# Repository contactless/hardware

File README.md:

hardware
========

Contactless Devices hardware repo

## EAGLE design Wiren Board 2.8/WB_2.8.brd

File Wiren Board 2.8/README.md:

Wiren Board 2.8
===============

Eagle source files.

The description is available here: http://contactless.ru/wiki/index.php/Wiren_Board_2.8

(c) 2013-2014 Contactless Devices, LLC
http://contactless.ru

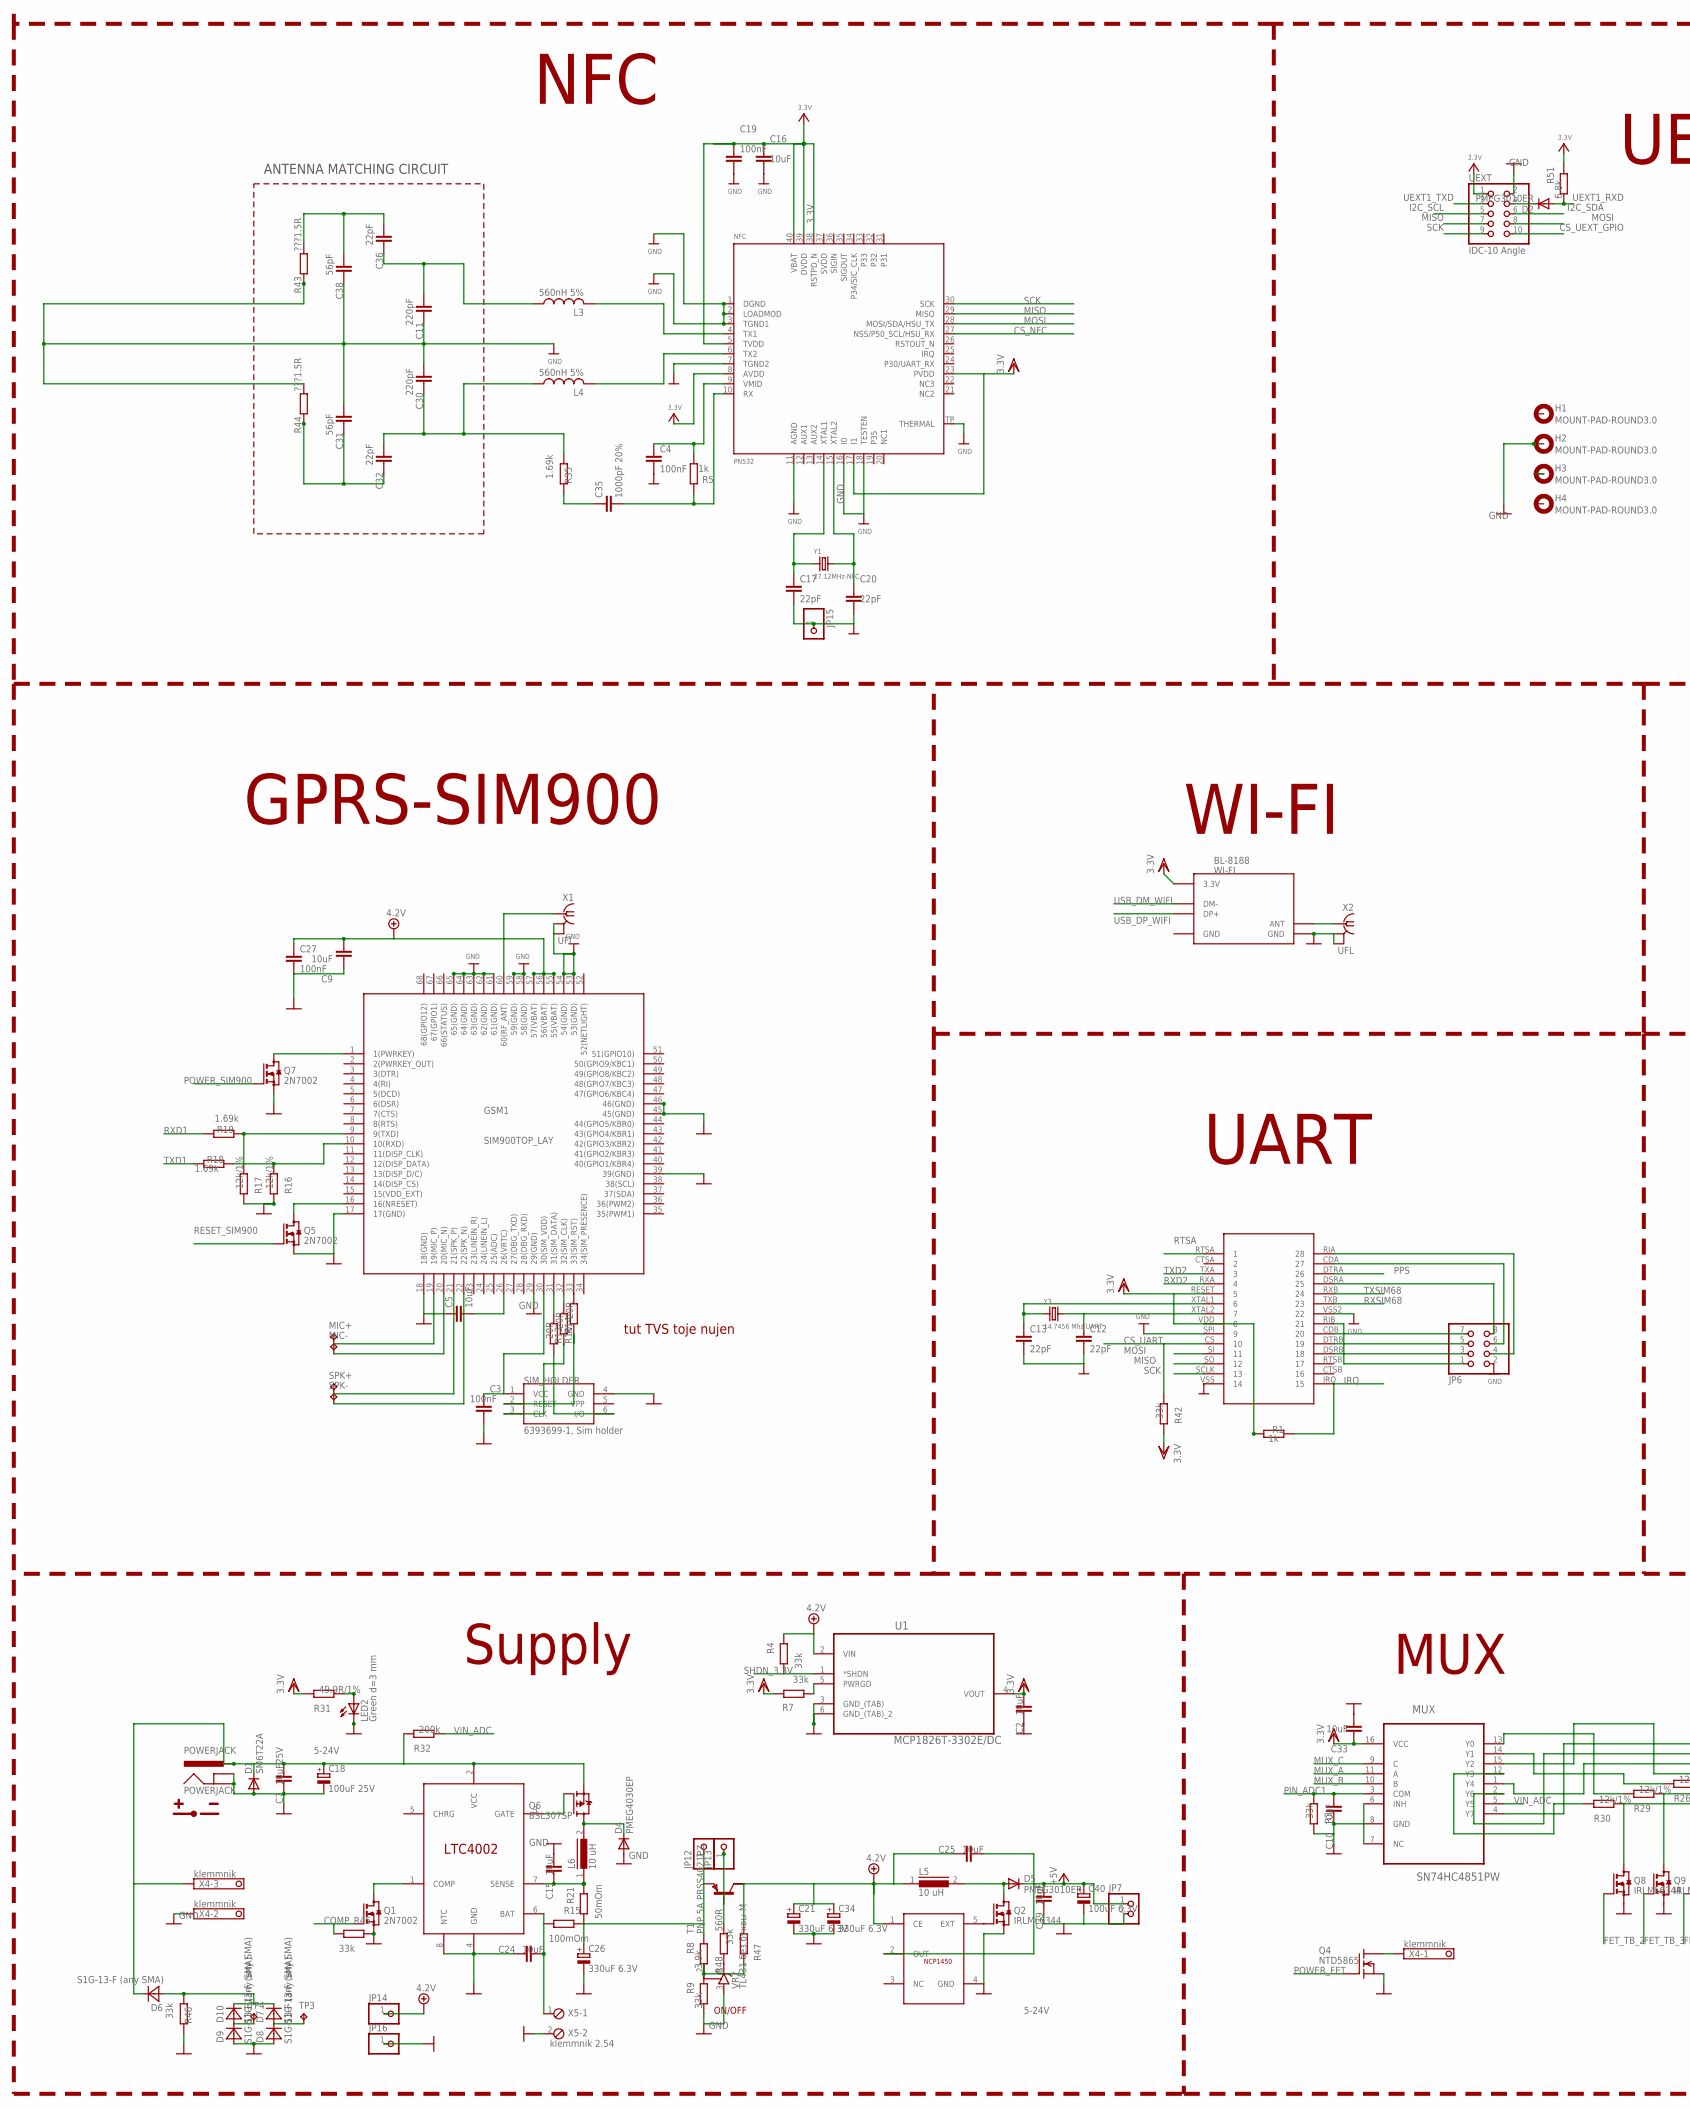
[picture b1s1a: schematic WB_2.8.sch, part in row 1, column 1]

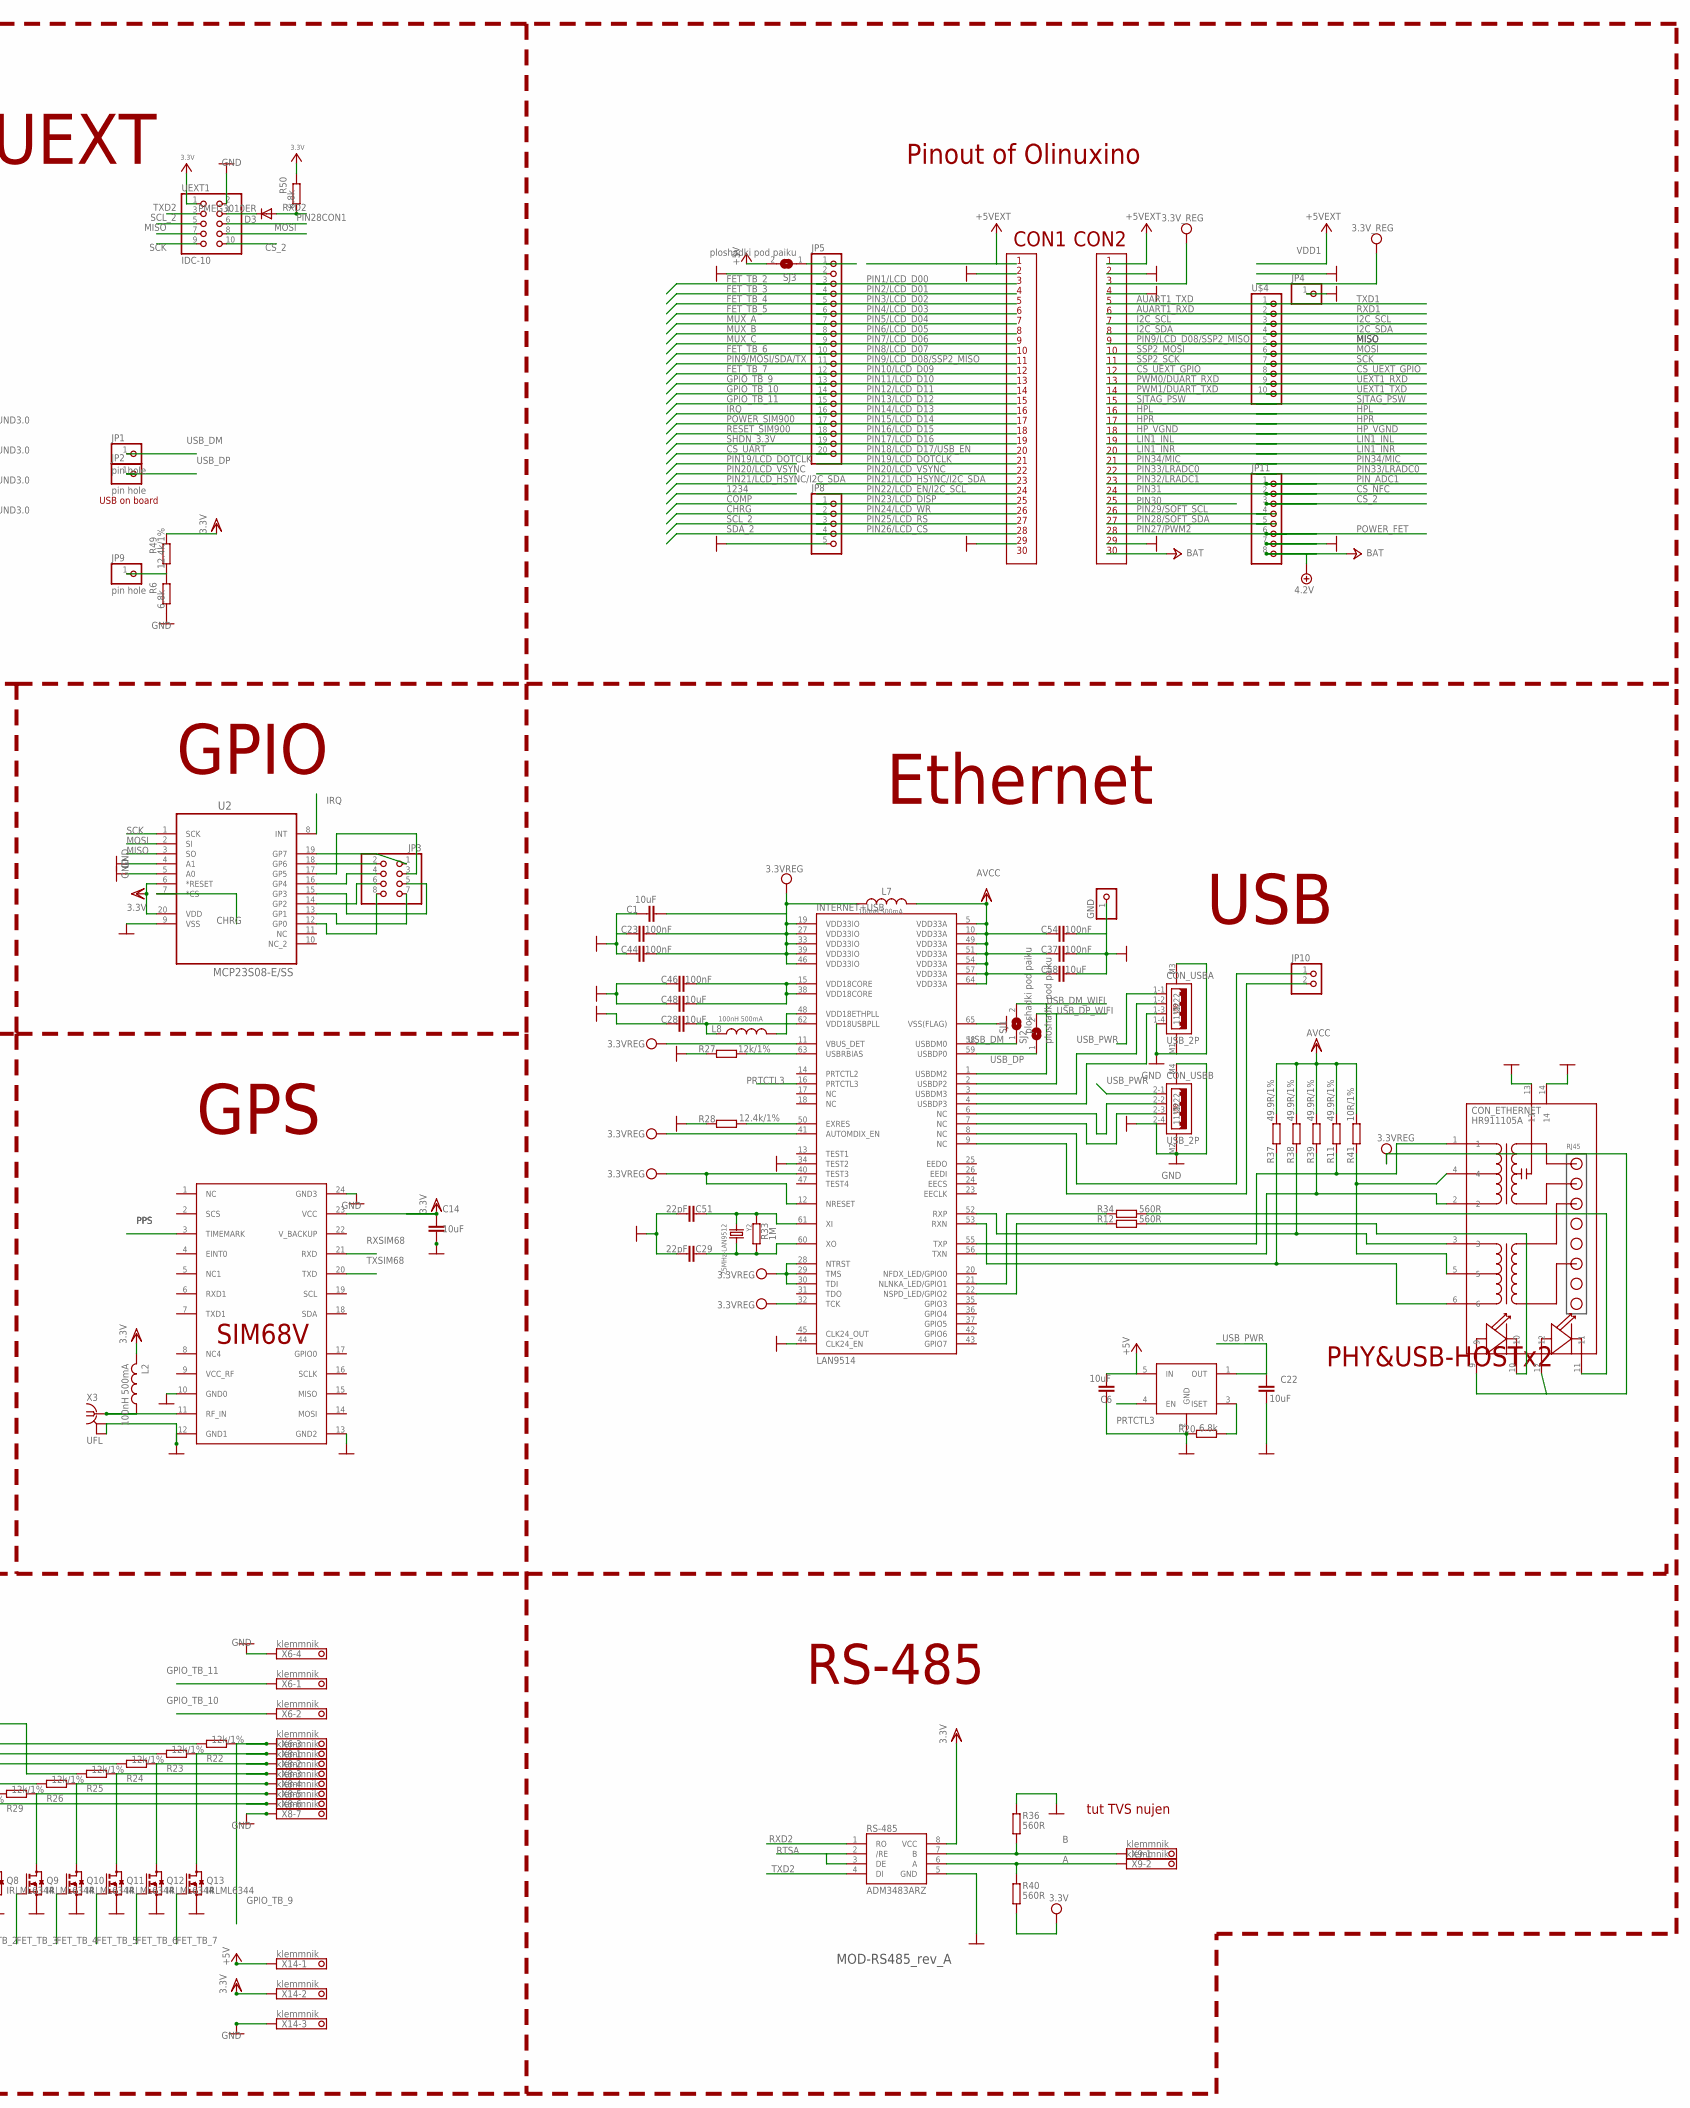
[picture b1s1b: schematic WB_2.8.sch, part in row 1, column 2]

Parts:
C1, C2, C5, C6, C9, C10, C14, C15, C16, C22, C24, C25, C28, C33, C39, C48, C58: 10uF; C0805_5MIL_D
C3, C4, C19, C23, C27, C37, C44, C46, C54: 100nF; C0805_5MIL_D
C7: 10uF25V; C0805_5MIL_D
C11, C30: 220pF; C0805_5MIL_D
C12, C13, C17, C20, C29, C32, C36, C51: 22pF; C0805_5MIL_D
C18: 100uF 25V; PANASONIC_D
C21, C26, C34: 330uF 6.3V; PANASONIC_D
C31, C38: 56pF; C0805_5MIL_D
C35: 1000pF 20%; C0805_5MIL_D
C40: 100uF 6.3V; PANASONIC_D
CON_ETHERNET: HR911105A
CON_USB: USB_2P; 2P
D1: SM6T22A; DO214AA
D2, D3, D5: PMEG3010ER; SOD123
D4: PMEG4030EP; DO214AC
D6, D7, D8, D9, D10: S1G-13-F (any SMA); SMA
GND: PINHD-1X1CB; 1X01-CLEANBIG
GSM1: SIM900TOP_LAY; SMT
H1, H2, H3, H4: MOUNT-PAD-ROUND3.0; 3,0-PAD
INTERNET+USB: LAN9514; QFN64
JP1, JP2: pin hole; 1X01@1
JP3, JP6: PINHD-2X4; 2X04
JP4, JP12, JP13: PINHD-1X1; 1X01
JP5: PINHD-1X20; 1X20
JP7, JP10: PINHD-1X2; 1X02
JP8: PINHD-1X5; 1X05
JP9: pin hole; 1X01
JP11: PINHD-1X8BIG; 1X08-BIG
JP14, JP16: PINHD-1X1; 1X01@1
JP15: PINHD-1X1CB; 1X01-CLEANBIG
L2, L7, L8: 100nH 500mA; L0805_5MIL_D
L3, L4: 560nH 5%; L0805_5MIL_D
L5, L6: 10 uH; DR74
LED2: Green d=3 mm; LED3MM
MIC+: PAD; TP20R
MIC-: PAD; TP20R
MUX: SN74HC4851PW; SOP65P640X120-16N
NFC: PN532; HVQFN40-6X6
POWERJACK: POWERJACK; 1
POWER_5V: NCP1450ASN50T1G; SO-6/4
Q1, Q5, Q7: 2N7002; SOT23
Q2, Q8, Q9, Q10, Q11, Q12, Q13: IRLML6344; SOT23
Q4: NTD5865; DPAK
Q6: BSL307SP; SC74_INFINEON
R1, R5: 1k; R0805_5MIL_D
R3, R4, R7, R9, R42, R45, R46, R47: 33k; R0805_5MIL_D
R6, R20, R50, R51: 6.8k; R0805_5MIL_D
R8: 3.9k; R0805_5MIL_D
R10, R13, R14: 20R; R0805_5MIL_D
R11, R31, R37, R38, R39: 49.9R/1%; R0805_5MIL_D
R12, R34, R36, R40, R48: 560R; R0805_5MIL_D
R15: 100mOm; R1206
R16, R17, R22, R23, R24, R25, R26, R27, R29, R30: 12k/1%; R0805_5MIL_D
R18, R19, R35: 1.69k; R0805_5MIL_D
R21: 50mOm; R1206
R28, R49: 12.4k/1%; R0805_5MIL_D
R32: 200k; R0805_5MIL_D
R33: 1M; R0805_5MIL_D
R41: 10R/1%; R0805_5MIL_D
R43, R44: ???1.5R; R0805_5MIL_D
RS-485: ADM3483ARZ; SOIC8
SIM68: SIM68; SIM68V
SIM_HOLDER: 6393699-1, Sim holder; BIGSIM
SJ1, SJ2, SJ3: ploshadki pod paiku; SJ
SPK+: PAD; TP20R
SPK-: PAD; TP20R
T1: PNP 5A PBSS4021PZ; SOT223
TP3, TP4: contact for POE; B1,27
U1: MCP1826T-3302E/DC; SOT230P700X180-6N
U2: MCP23S08-E/SS; SOP65P780X200-20N
U$3: LTC4002ES8-4.2; SOIC-8
U$4: PINHD-1X10; 1X10-BIG
U$15: SY6280; SOT23-5L
UART: !SC16IS752; TSSOP28
UEXT: IDC-10 Angle; 2X05/90
UEXT1: IDC-10; 2X05
VR2: TL431 без буквы M; SOT23
WI-FI: BL-8188; BL-8188-PACK
X1, X2, X3: UFL; MC-921
X4, X14: klemmnik; 1751251
X5: klemmnik 2.54; 2POL254
X6: klemmnik; 1751264
X8: klemmnik; 1751293
X9: klemmnik; 1751248
Y1: 27.12MHz-NFC; CRYSTAL_3.2X2.5
Y2: 25MHz-LAN9512; CRYSTAL_3.2X2.5
Y3: 14.7456 Mhz UART; CRYSTAL_3.2X2.5

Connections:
3.3V: C1.2, C2.2, C14.1, C16.1, C19.1, C23.2, C33.1, C44.2, CON_ETHERNET.9, CON_ETHERNET.12, INTERNET+USB.11 (VBUS_DET), INTERNET+USB.12 (NRESET), INTERNET+USB.19 (VDD33IO), INTERNET+USB.27 (VDD33IO), INTERNET+USB.28 (NTRST), INTERNET+USB.29 (TMS), INTERNET+USB.30 (TDI), INTERNET+USB.32 (TCK), INTERNET+USB.33 (VDD33IO), INTERNET+USB.39 (VDD33IO), INTERNET+USB.40 (TEST3), INTERNET+USB.41 (AUTOMDIX_EN), INTERNET+USB.46 (VDD33IO), L2.2, L7.1, MUX.16 (VCC), NFC.5 (TVDD), NFC.8 (AVDD), NFC.17 (I1), NFC.23 (PVDD), NFC.38 (RSTPD_N), NFC.39 (DVDD), NFC.40 (VBAT), R1.2, R7.2, R31.1, R40.1, R42.1, R49.2, R50.2, R51.2, RS-485.8 (VCC), SIM68.23 (VCC), U1.4 (VOUT), U2.6 (*RESET), U2.20 (VDD), UART.RESET (5), UART.VDD (8), UEXT.1, UEXT1.1, WI-FI.3.3V, X14.2
5-24V: C7.2, C18.+, D1.C, D6.C, POWERJACK.1 (PWR), Q6.4 (S), R32.1, U$3.2 (VCC), X4.3
15(VDD_EXT): GSM1.15 (15(VDD_EXT))
+4.1V: C9.2, C21.+, C25.1, C27.1, C34.+, GSM1.55 (55(VBAT)), GSM1.56 (56(VBAT)), GSM1.57 (57(VBAT)), JP11.8, JP14.1, L5.1, POWER_5V.1 (CE), R4.2, R47.1, T1.4 (C1), U1.2 (VIN)
+5V: C6.1, C25.2, C39.2, C40.+, D5.C, JP7.1, POWER_5V.2 (OUT), SJ3.2, U$15.5 (IN), X14.1
A: R40.2, RS-485.6 (A), X9.2
B: R36.1, RS-485.7 (B), X9.1
CHRG: JP8.2, U2.7 (*CS)
COMP: JP8.1, Q1.1 (G), R45.1
CS_2: JP11.3, UEXT1.10
CS_NFC: JP11.2, NFC.27 (NSS/P50_SCL/HSU_RX)
CS_UART: JP5.20, R42.2, UART.CS (10)
CS_UEXT_GPIO: U$4.8, UEXT.10
DFGSDFG: Q13.3 (D), R23.2, X8.1
DFTGSDFG: MUX.15 (Y2), R25.1
ERTERVT: MUX.12 (Y3), R30.1
FDSGSDFGSDF: JP11.5
FET_TB_2: JP5.3, Q8.1 (G)
FET_TB_3: JP5.4, Q9.1 (G)
FET_TB_4: JP5.5, Q10.1 (G)
FET_TB_5: JP5.6, Q11.1 (G)
FET_TB_6: JP5.10, Q12.1 (G)
FET_TB_7: JP5.12, Q13.1 (G)
GND: C1.1, C2.1, C3.2, C4.2, C5.1, C6.2, C7.1, C9.1, C10.1, C11.1, C12.2, C13.2, C14.2, C15.2, C16.2, C17.2, C18.-, C19.2, C20.2, C21.-, C22.2, C23.1, C24.1, C26.-, C27.2, C28.1, C29.2, C30.2, C31.2, C33.2, C34.-, C37.2, C38.1, C39.1, C40.-, C44.1, C46.1, C48.1, C51.2, C54.2, C58.2, CON_ETHERNET.13, CON_ETHERNET.14, CON_USB.1-4 (4), CON_USB.2-4 (4), CON_USB.M1 (1111), CON_USB.M2 (1111), CON_USB.M3 (2222), CON_USB.M4 (2222), D1.A, D4.A, D8.A, D9.A, GND.1, GSM1.17 (17(GND)), GSM1.18 (18(GND)), GSM1.29 (29(GND)), GSM1.39 (39(GND)), GSM1.45 (45(GND)), GSM1.46 (46(GND)), GSM1.53 (53(GND)), GSM1.54 (54(GND)), GSM1.58 (58(GND)), GSM1.59 (59(GND)), GSM1.61 (61(GND)), GSM1.62 (62(GND)), GSM1.63 (63(GND)), GSM1.64 (64(GND)), GSM1.65 (65(GND)), H2.B3,0, INTERNET+USB.34 (TEST2), INTERNET+USB.44 (CLK24_EN), INTERNET+USB.65 (VSS(FLAG)), JP4.1, JP5.2, JP6.2, JP7.2, JP8.5, JP11.7, JP15.1, JP16.1, LED2.K (C), MUX.6 (INH), MUX.7 (NC), MUX.8 (GND), NFC.1 (DGND), NFC.2 (LOADMOD), NFC.3 (TGND1), NFC.7 (TGND2), NFC.11 (AGND), NFC.16 (I0), NFC.18 (TESTEN), NFC.TP (THERMAL), POWERJACK.P$1 (GNDBREAK), POWERJACK.P$5 (GND), POWER_5V.4 (GND), Q1.2 (S), Q2.2 (S), Q4.3 (S), Q5.2 (S), Q7.2 (S), Q8.2 (S), Q9.2 (S), Q10.2 (S), Q11.2 (S), Q12.2 (S), Q13.2 (S), R3.1, R6.1, R9.1, R16.1, R17.1, R20.1, R27.1, R28.1, R36.2, R43.1, R44.2, R45.2, R46.1, RS-485.5 (GND), SIM68.10 (GND0), SIM68.12 (GND1), SIM68.13 (GND2), SIM68.24 (GND3), SIM_HOLDER.4 (GND), U1.3 (GND_(TAB)), U1.6 (GND_(TAB)_2), U2.4 (A1), U2.5 (A0), U2.9 (VSS), U$3.4 (GND), U$3.8 (NTC), U$15.2 (GND), UART.SPI (9), UART.VSS (14), UART.VSS2 (22), UEXT.2, UEXT1.2, VR2.3 (A), WI-FI.GND1 (GND), WI-FI.GND2 (GND), X1.2@1 (GND), X1.2@2 (GND), X2.2@1 (GND), X2.2@2 (GND), X3.2@1 (GND), X3.2@2 (GND), X4.2, X5.2, X6.4, X8.7, X14.3
GPIO_TB_9: JP5.13, R22.2, X6.3
GPIO_TB_10: JP5.14, X6.2
GPIO_TB_11: JP5.15, X6.1
I2C_SCL: U$4.3, UEXT.5
I2C_SDA: U$4.4, UEXT.6
IRQ: JP5.16, R1.1, U2.8 (INT), UART.IRQ (15)
MISO: NFC.29 (MISO), U2.3 (SO), U$4.5, UART.SO (12), UEXT.7, UEXT1.7
MOSI: NFC.28 (MOSI/SDA/HSU_TX), U2.2 (SI), U$4.6, UART.SI (11), UEXT.8, UEXT1.8
MUX_A: JP5.7, MUX.11 (A)
MUX_B: JP5.8, MUX.10 (B)
MUX_C: JP5.9, MUX.9 (C)
unnamed: L3.2, NFC.4 (TX1)
unnamed: L4.2, NFC.6 (TX2)
unnamed: C11.2, C36.1, L3.1
unnamed: GSM1.16 (16(NRESET)), Q5.3 (D)
unnamed: JP13.1, R48.2, T1.1 (B)
unnamed: GSM1.9 (9(TXD)), R17.2, R19.1
unnamed: C17.1, NFC.14 (XTAL1), Y1.1
unnamed: C20.1, NFC.15 (XTAL2), Y1.2
unnamed: C35.1, R35.1
unnamed: C4.1, NFC.9 (VMID), R5.2
unnamed: C35.2, NFC.10 (RX), R5.1
unnamed: C30.1, C32.2, L4.1, R35.2
unnamed: R10.1, SIM_HOLDER.6 (I/O)
unnamed: GSM1.33 (33(SIM_RST)), R14.2
unnamed: R13.1, SIM_HOLDER.3 (CLK)
unnamed: WI-FI.ANT, X2.1
unnamed: R14.1, SIM_HOLDER.2 (RESET)
unnamed: C26.+, JP12.1, R8.2, R15.2, R21.1, T1.3 (E)
unnamed: GSM1.31 (31(SIM_DATA)), R10.2
unnamed: GSM1.1 (1(PWRKEY)), Q7.3 (D)
unnamed: C5.2, GSM1.26 (26(VRTC))
unnamed: GSM1.60 (60(RF_ANT)), X1.1
unnamed: Q6.3 (G), U$3.3 (GATE)
unnamed: C46.2, C48.2, INTERNET+USB.15 (VDD18CORE), INTERNET+USB.38 (VDD18CORE)
unnamed: JP6.3, UART.DSRB (18)
unnamed: GSM1.32 (32(SIM_CLK)), R13.2
unnamed: L2.1, SIM68.11 (RF_IN), X3.1
unnamed: C13.1, UART.XTAL1 (6), Y3.1
unnamed: C12.1, UART.XTAL2 (7), Y3.2
unnamed: C3.1, GSM1.30 (30(SIM_VDD)), SIM_HOLDER.1 (VCC)
unnamed: Q4.4 (D), X4.1
unnamed: GSM1.10 (10(RXD)), R16.2, R18.1
unnamed: JP3.1, U2.19 (GP7)
unnamed: INTERNET+USB.48 (VDD18ETHPLL), L8.2
unnamed: C28.2, INTERNET+USB.62 (VDD18USBPLL), L8.1
unnamed: INTERNET+USB.63 (USBRBIAS), R27.2
unnamed: INTERNET+USB.50 (EXRES), R28.2
unnamed: R48.1, VR2.1 (C)
unnamed: MUX.1 (Y4), R24.1
unnamed: R20.2, U$15.3 (ISET)
unnamed: Q12.3 (D), R24.2, X8.2
unnamed: Q11.3 (D), R25.2, X8.3
unnamed: Q10.3 (D), R26.2, X8.4
unnamed: Q9.3 (D), R29.2, X8.5
unnamed: Q8.3 (D), R30.2, X8.6
unnamed: C15.1, L6.1, R21.2, U$3.7 (SENSE)
unnamed: MUX.4 (Y7), R22.1
unnamed: MUX.2 (Y6), R23.1
unnamed: D7.A, D8.C, TP3.TP
unnamed: LED2.A, R31.2
unnamed: MUX.14 (Y1), R26.1
unnamed: D4.C, L6.2, Q6.1 (D), Q6.2 (D), Q6.5 (D), Q6.6 (D)
unnamed: C51.1, INTERNET+USB.61 (XI), R33.2, Y2.1
unnamed: C29.1, INTERNET+USB.60 (XO), R33.1, Y2.2
unnamed: INTERNET+USB.21 (NLNKA_LED/GPIO1), R34.1
unnamed: INTERNET+USB.22 (NSPD_LED/GPIO2), R12.1
unnamed: CON_ETHERNET.11, R34.2
unnamed: POWER_5V.5 (EXT), Q2.1 (G)
unnamed: CON_ETHERNET.6, INTERNET+USB.53 (RXN), R37.1
unnamed: CON_ETHERNET.3, INTERNET+USB.52 (RXP), R38.1
unnamed: CON_ETHERNET.2, INTERNET+USB.56 (TXN), R39.1
unnamed: CON_ETHERNET.1, INTERNET+USB.55 (TXP), R11.1
unnamed: CON_ETHERNET.4, CON_ETHERNET.5, R41.1
unnamed: CON_USB.1-2 (2), INTERNET+USB.3 (USBDM3)
unnamed: CON_USB.1-3 (3), INTERNET+USB.4 (USBDP3)
unnamed: CON_USB.2-2 (2), INTERNET+USB.6 (NC)
unnamed: CON_USB.2-3 (3), INTERNET+USB.7 (NC)
unnamed: D9.C, D10.A, TP4.TP
unnamed: GSM1.19 (19(MIC_P)), MIC+.TP
unnamed: GSM1.20 (20(MIC_N)), MIC-.TP
unnamed: D5.A, L5.2, Q2.3 (D)
unnamed: D6.A, D7.C, D10.C, R46.2
unnamed: CON_ETHERNET.10, R12.2
unnamed: GSM1.21 (21(SPK_P)), SPK+.TP
unnamed: GSM1.22 (22(SPK_N)), SPK-.TP
unnamed: Q1.3 (D), U$3.1 (COMP)
unnamed: R8.1, R9.2, R47.2, VR2.2 (R)
unnamed: JP9.1, R6.2, R49.1
unnamed: INTERNET+USB.8 (NC), JP10.1
unnamed: INTERNET+USB.9 (NC), JP10.2
unnamed: JP6.1, UART.RIB (21)
unnamed: JP6.5, UART.DTRB (19)
unnamed: JP6.7, UART.CDB (20)
unnamed: MUX.13 (Y0), R29.1
unnamed: C24.2, R15.1, U$3.6 (BAT), X5.1
unnamed: R7.1, U1.5 (PWRGD)
unnamed: JP3.2, U2.18 (GP6)
unnamed: JP3.3, U2.17 (GP5)
unnamed: JP6.8, UART.DSRA (25)
unnamed: JP6.6, UART.CDA (27)
unnamed: JP6.4, UART.RIA (28)
unnamed: JP3.4, U2.16 (GP4)
unnamed: JP3.5, U2.15 (GP3)
unnamed: JP3.6, U2.14 (GP2)
unnamed: JP3.7, U2.13 (GP1)
unnamed: JP3.8, U2.12 (GP0)
unnamed: JP5.1, SJ3.1
unnamed: D2.C, UEXT.4
unnamed: D3.C, UEXT1.4
PIN9/MOSI/SDA/TX: JP5.11
PIN28CON1: UEXT1.6
PIN29/SOFT_SCL: JP11.4
PIN_ADC1: C10.2, JP11.1, MUX.3 (COM), R3.2
POWER_FET: JP11.6, Q4.1 (G)
POWER_SIM900: JP5.17, Q7.1 (G)
PPS: SIM68.3 (TIMEMARK), UART.DTRA (26)
PRTCTL3: INTERNET+USB.16 (PRTCTL3), U$15.4 (EN)
RESET_SIM900: JP5.18, Q5.1 (G)
RTSA: RS-485.2 (/RE), RS-485.3 (DE), UART.RTSA (1)
RXD1: R19.2, U$4.2
RXD2: D3.A, R50.1, RS-485.1 (RO), UART.RXA (4)
RXSIM68: SIM68.21 (RXD), UART.TXB (23)
SCK: NFC.30 (SCK), U2.1 (SCK), U$4.7, UART.SCLK (13), UEXT.9, UEXT1.9
SCL_2: JP8.3, UEXT1.5
SDA_2: JP8.4
SHDN_3.3V: JP5.19, R4.1, U1.1 (*SHDN)
TX1_ANTENNA: C36.2, C38.2, R43.2
TX2_ANTENNA: C31.1, C32.1, R44.1
TXD1: R18.2, U$4.1
TXD2: RS-485.4 (DI), UART.TXA (3), UEXT1.3
TXSIM68: SIM68.20 (TXD), UART.RXB (24)
UEXT1_RXD: D2.A, R51.1, U$4.9
UEXT1_TXD: U$4.10, UEXT.3
USB_DM: INTERNET+USB.58 (USBDM0), JP1.1, SJ1.1
USB_DM_WIFI: INTERNET+USB.1 (USBDM2), SJ1.2, WI-FI.DM-
USB_DP: INTERNET+USB.59 (USBDP0), JP2.1, SJ2.1
USB_DP_WIFI: INTERNET+USB.2 (USBDP2), SJ2.2, WI-FI.DP+
USB_PWR: C22.1, CON_USB.1-1 (1), CON_USB.2-1 (1), U$15.1 (OUT)
VCC_RF: SIM68.9 (VCC_RF)
VDD: C37.1, C54.1, C58.1, INTERNET+USB.5 (VDD33A), INTERNET+USB.10 (VDD33A), INTERNET+USB.49 (VDD33A), INTERNET+USB.51 (VDD33A), INTERNET+USB.54 (VDD33A), INTERNET+USB.57 (VDD33A), INTERNET+USB.64 (VDD33A), L7.2, R11.2, R37.2, R38.2, R39.2, R41.2
VIN_ADC: MUX.5 (Y5), R32.2

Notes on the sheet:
ANTENNA MATCHING CIRCUIT
NFC
UEXT
GPRS-SIM900
WI-FI
UART
GPS
Ethernet
USB
PHY&USB-HOSTx2
Supply
MUX
MOD-RS485_rev_A
RS-485
USB on board
ON/OFF
Pinout of Olinuxino
CON1
CON2
GPIO
tut TVS nujen
tut TVS toje nujen

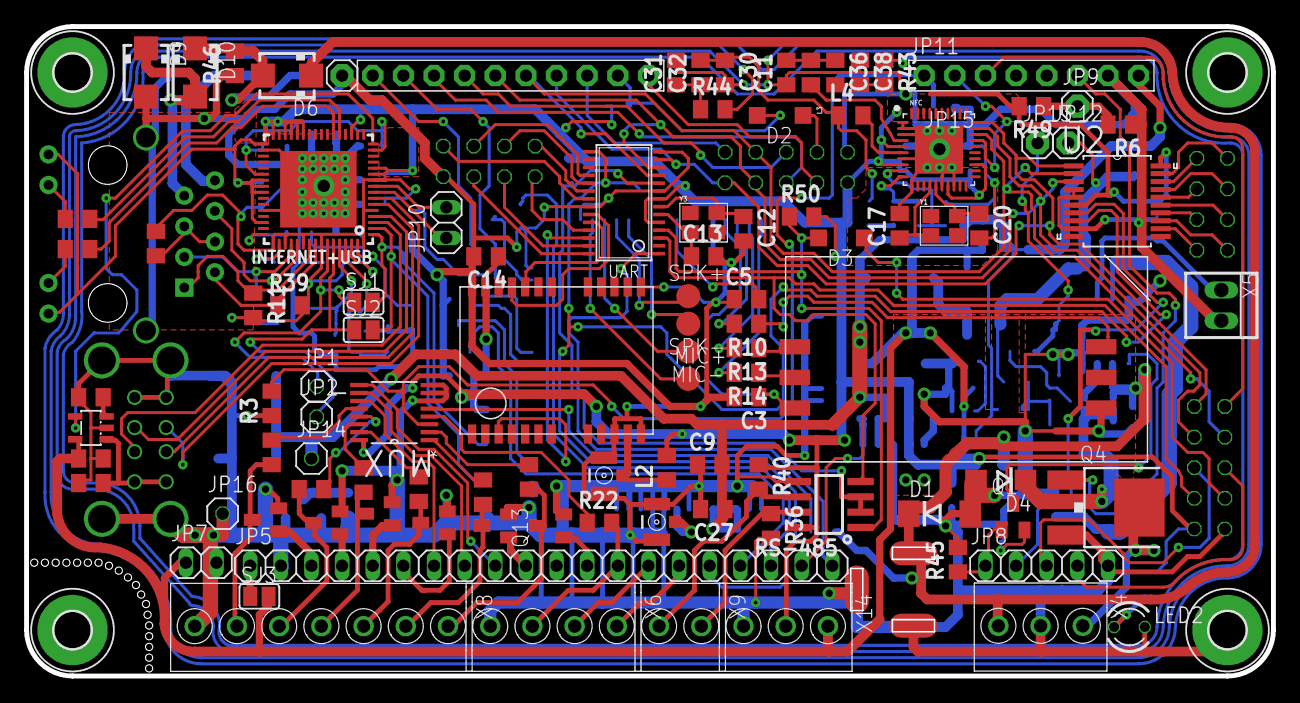
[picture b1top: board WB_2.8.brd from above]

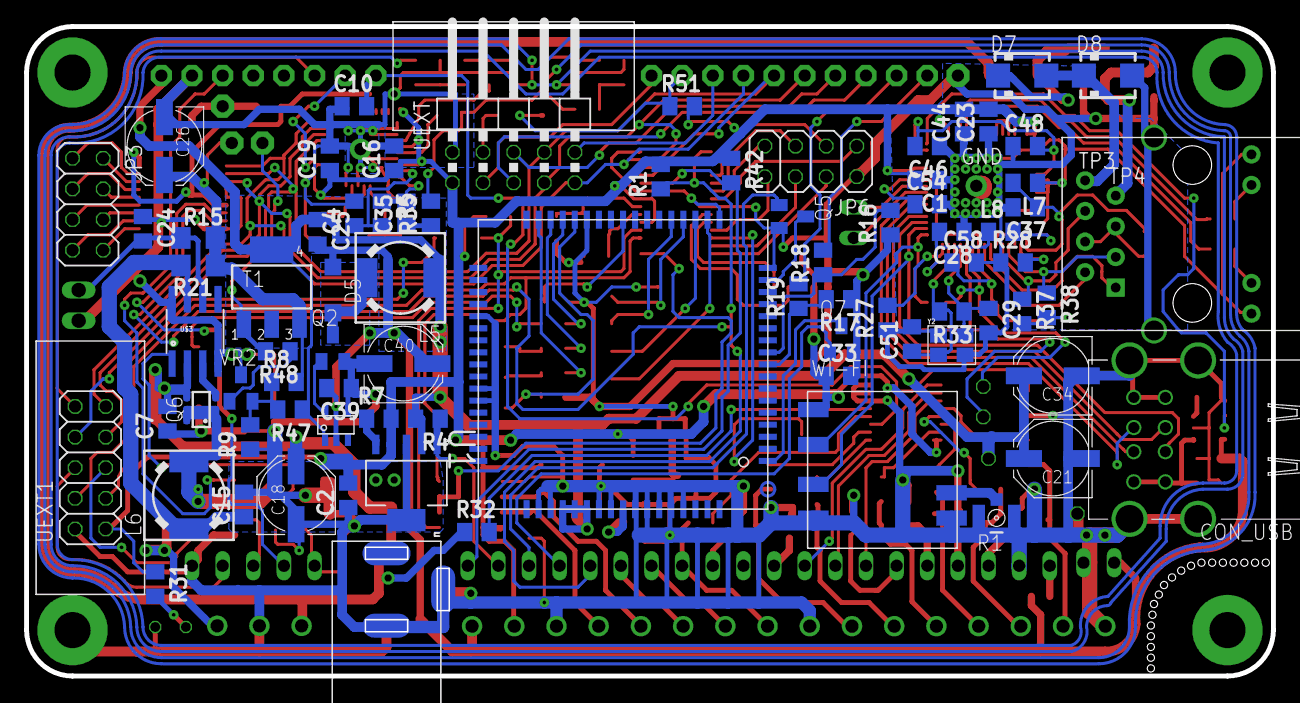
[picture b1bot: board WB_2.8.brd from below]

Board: 2 copper layers, 103.4 x 53.8 mm, 189 parts (82 on the bottom side), 159 nets.

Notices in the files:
parts and their libraries:
microbuilder: This work is placed in the public domain, and may be freely used for commercial and non-commercial work with the following conditions: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
